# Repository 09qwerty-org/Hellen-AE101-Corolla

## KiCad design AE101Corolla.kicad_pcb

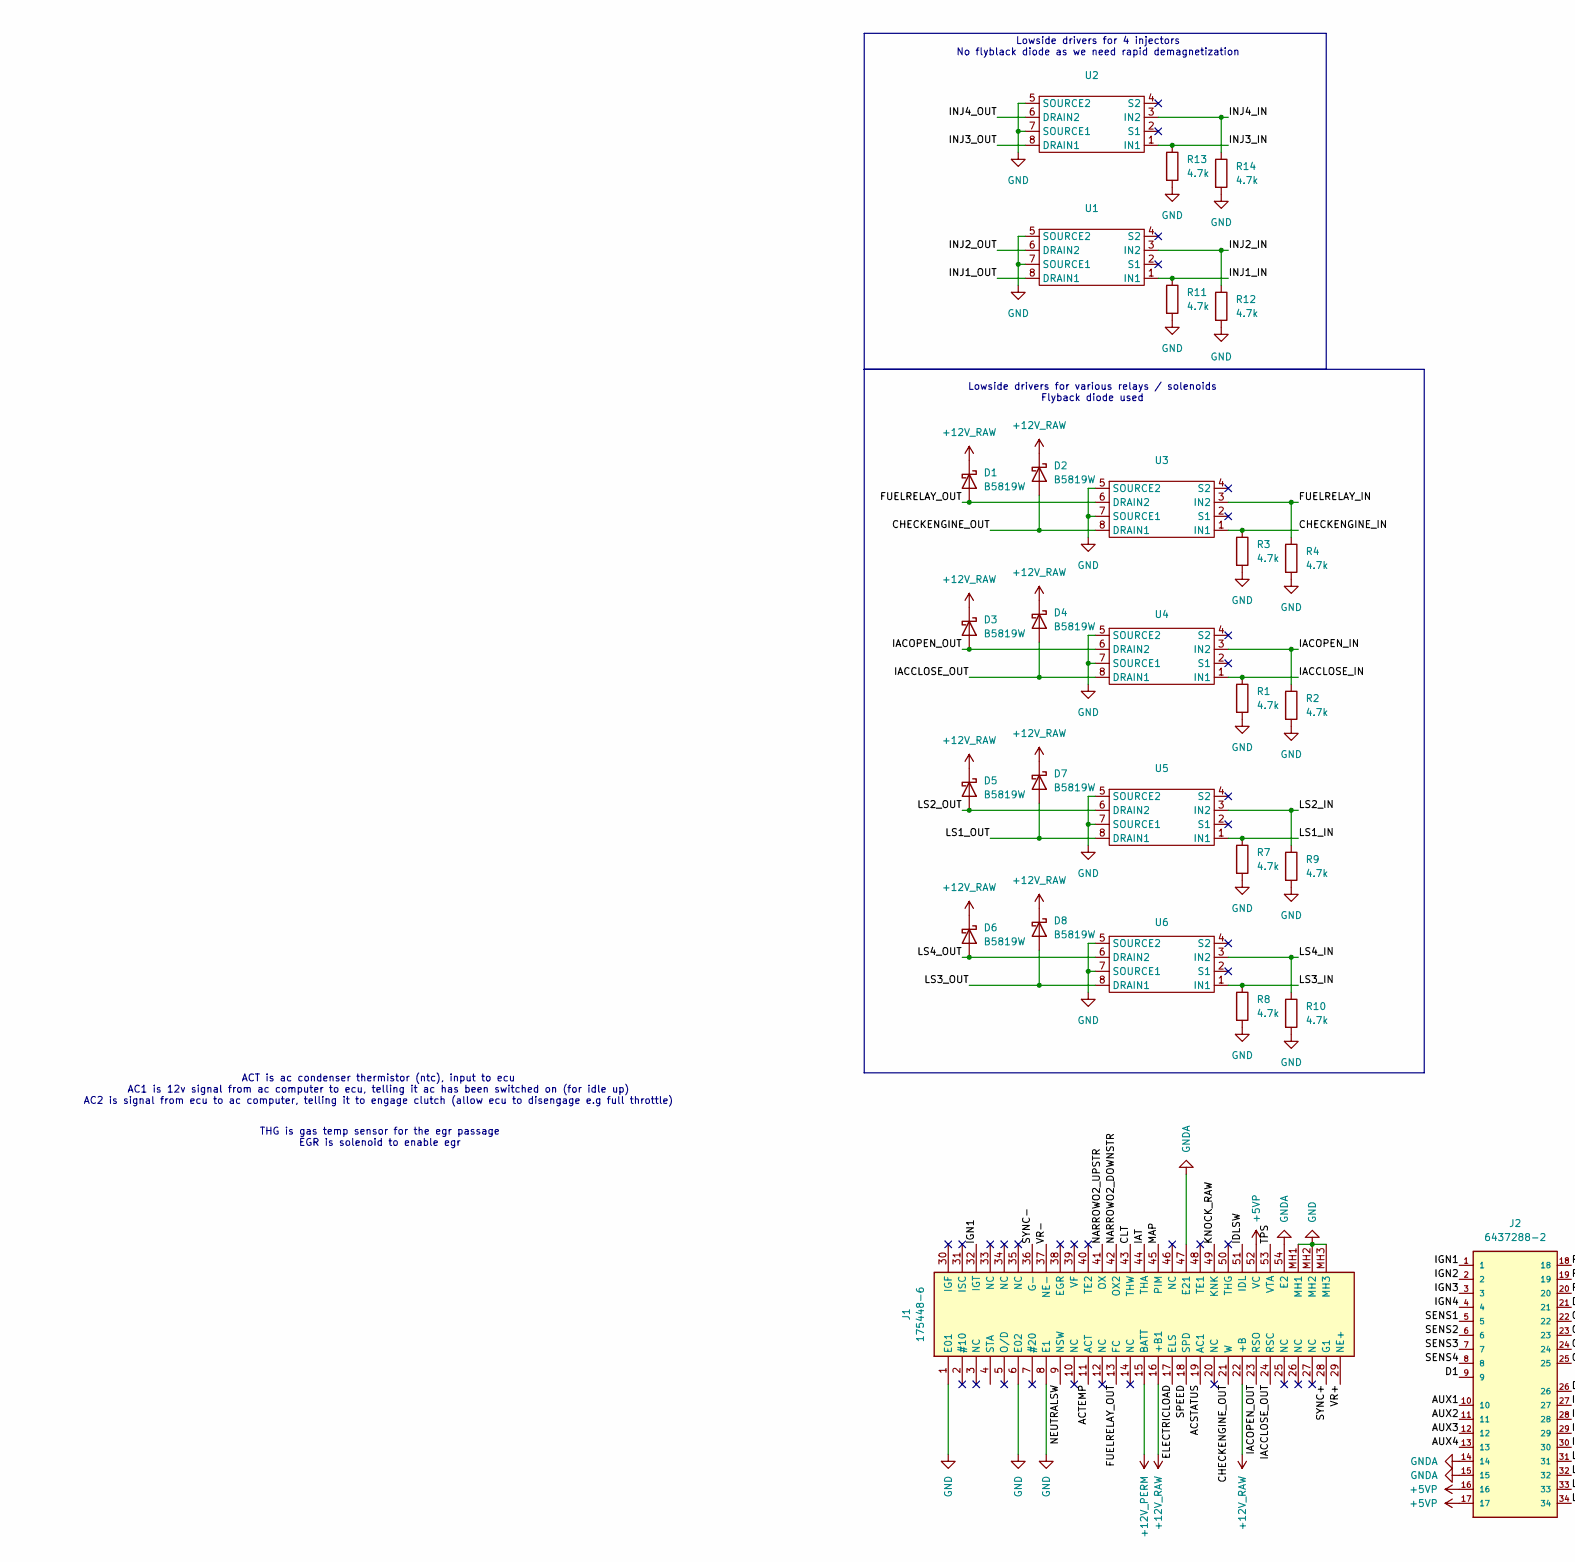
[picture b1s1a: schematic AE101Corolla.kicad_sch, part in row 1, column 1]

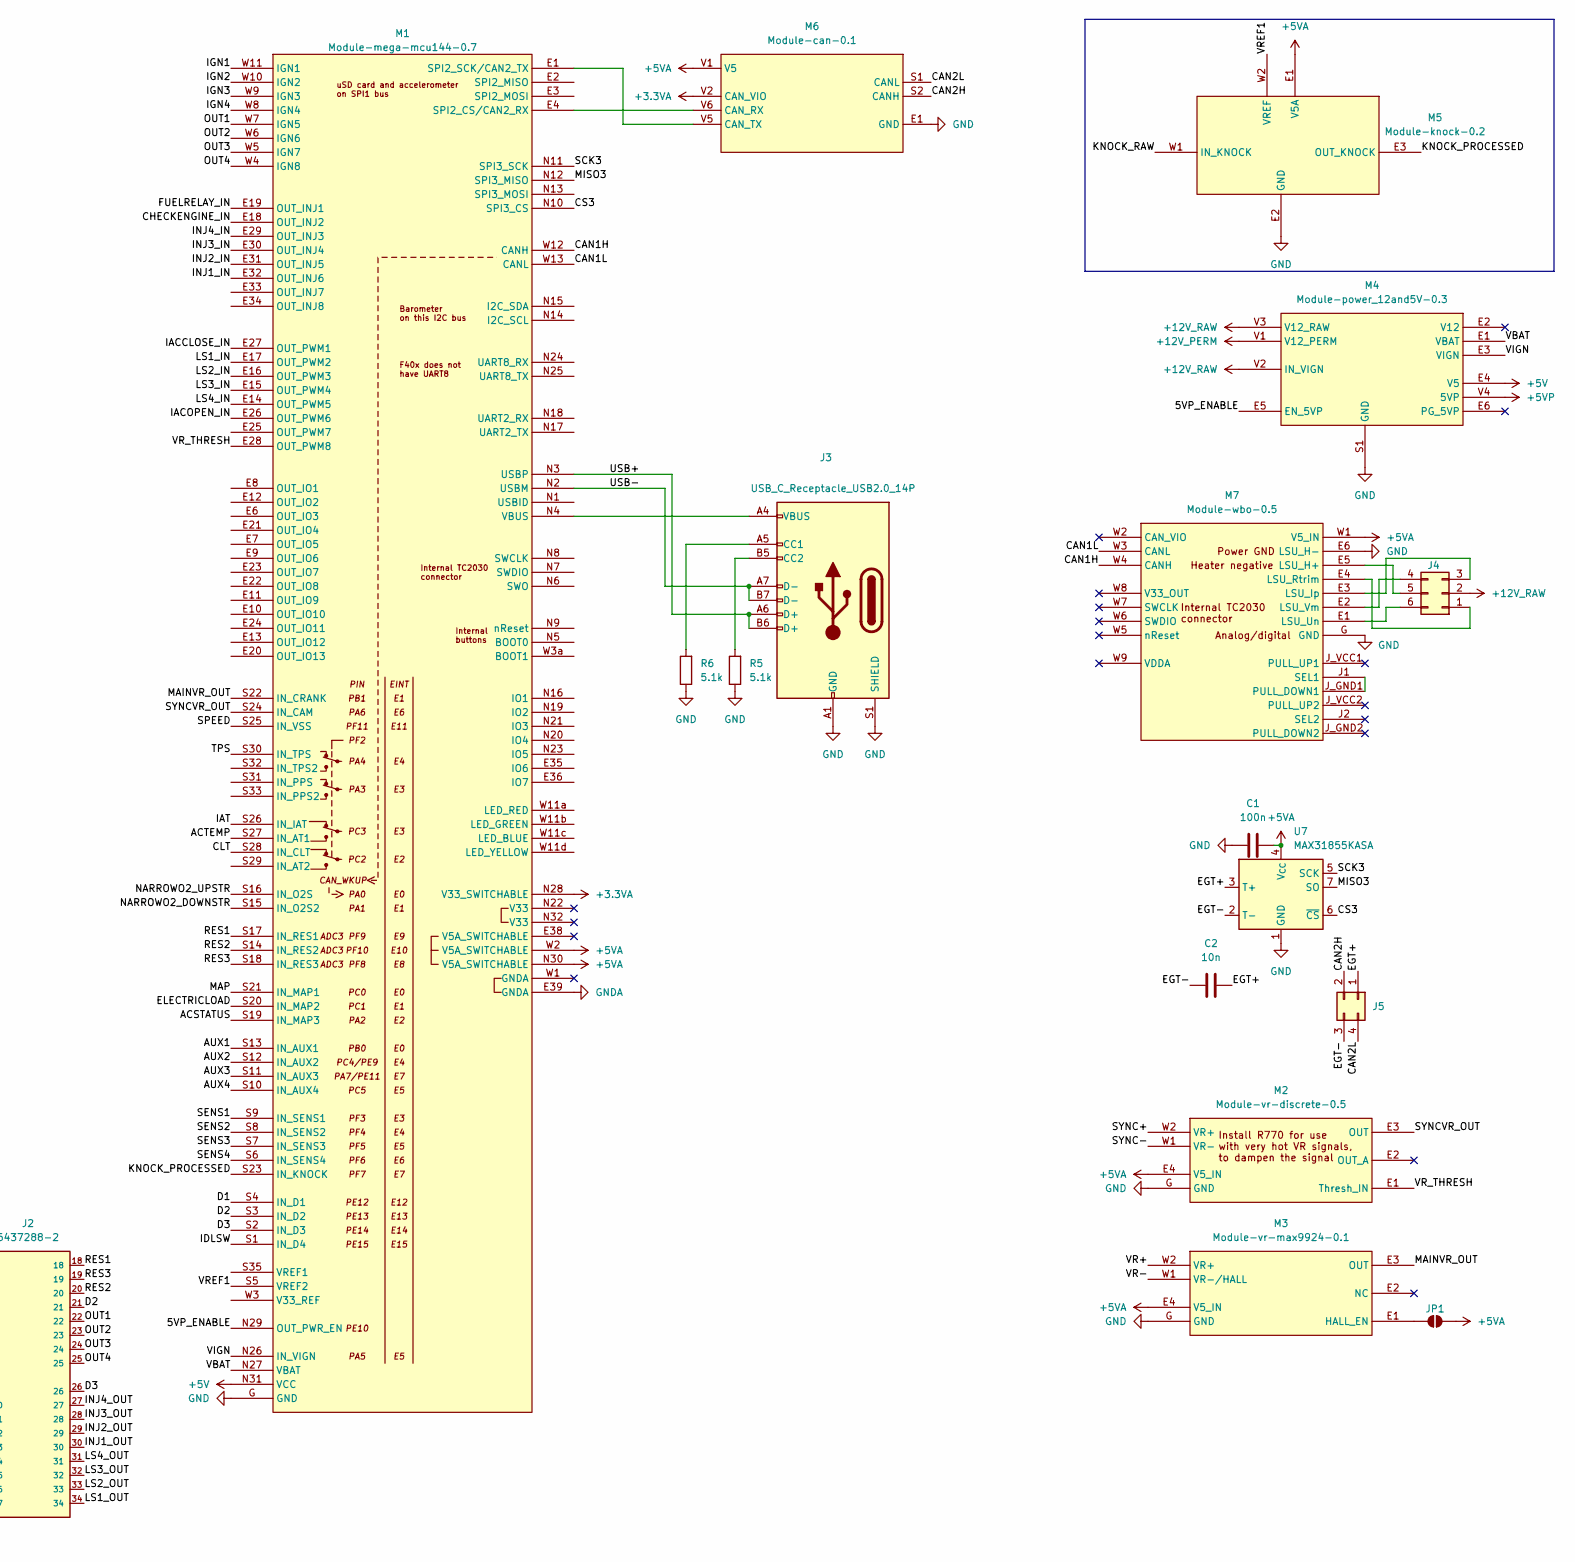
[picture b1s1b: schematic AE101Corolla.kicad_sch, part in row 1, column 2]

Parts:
C1: 100n; C_0402_1005Metric; LCSC C1525
C2: 10n; C_0402_1005Metric; LCSC C15195
D1, D2, D3, D4, D5, D6, D7, D8: B5819W; D_SOD-123; LCSC C8598
J1: 175448-6; 1754486; Mouser Part Number 571-175448-6
J2: 6437288-2; TE_6437288-2; PARTREV A1
J3: USB_C_Receptacle_USB2.0_14P; USB_C_Receptacle_GCT_USB4105-xx-A_16P_TopMnt_Horizontal
J4: Conn_02x03_Counter_Clockwise; Molex_Mini-Fit_Jr_5569-06A2_2x03_P4.20mm_Horizontal
J5: Conn_02x02_Counter_Clockwise; Molex_Mini-Fit_Jr_5569-04A2_2x02_P4.20mm_Horizontal
JP1: SolderJumper_2_Open; SolderJumper-2_P1.3mm_Open_TrianglePad1.0x1.5mm
M1: Module-mega-mcu144-0.7; mega-mcu144
M2: Module-vr-discrete-0.5; vr-discrete
M3: Module-vr-max9924-0.1; vr-max9924
M4: Module-power_12and5V-0.3; power_12and5V
M5: Module-knock-0.2; knock
M6: Module-can-0.1; can
M7: Module-wbo-0.5; wbo
R1, R2, R3, R4, R7, R8, R9, R10, R11, R12, R13, R14: 4.7k; R_0402_1005Metric; LCSC C25900
R5, R6: 5.1k; R_0402_1005Metric; LCSC C144745
U1, U2, U3, U4, U5, U6: VNLD5090-E; LCSC C222209
U7: MAX31855KASA; SOIC-8_3.9x4.9mm_P1.27mm

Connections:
+3.3VA: M1.N28 (V33_SWITCHABLE), M6.V2 (CAN_VIO)
+5V: M1.N31 (VCC), M4.E4 (V5)
+5VA: C1.1, JP1.2 (B), M1.N30 (V5A_SWITCHABLE), M1.W2 (V5A_SWITCHABLE), M2.E4 (V5_IN), M3.E4 (V5_IN), M5.E1 (V5A), M6.V1 (V5), M7.W1 (V5_IN), U7.4 (V_{CC})
+5VP: J1.52 (VC), J2.16, J2.17, M4.V4 (5VP)
+12V_PERM: J1.15 (BATT), M4.V1 (V12_PERM)
+12V_RAW: D1.1 (K), D2.1 (K), D3.1 (K), D4.1 (K), D5.1 (K), D6.1 (K), D7.1 (K), D8.1 (K), J1.16 (+B1), J1.22 (+B), J4.2, M4.V2 (IN_VIGN), M4.V3 (V12_RAW)
/5VP_ENABLE: M1.N29 (OUT_PWR_EN), M4.E5 (EN_5VP)
/ACSTATUS: J1.19 (AC1), M1.S19 (IN_MAP3)
/ACTEMP: J1.11 (ACT), M1.S27 (IN_AT1)
/AUX1: J2.10, M1.S13 (IN_AUX1)
/AUX2: J2.11, M1.S12 (IN_AUX2)
/AUX3: J2.12, M1.S11 (IN_AUX3)
/AUX4: J2.13, M1.S10 (IN_AUX4)
/CAN1H: M1.W12 (CANH), M7.W4 (CANH)
/CAN1L: M1.W13 (CANL), M7.W3 (CANL)
/CAN2H: J5.2, M6.S2 (CANH)
/CAN2L: J5.4, M6.S1 (CANL)
/CHECKENGINE_IN: M1.E18 (OUT_INJ2), R3.1, U3.1 (IN1)
/CHECKENGINE_OUT: D2.2 (A), J1.21 (W), U3.8 (DRAIN1)
/CLT: J1.43 (THW), M1.S28 (IN_CLT)
/CS3: M1.N10 (SPI3_CS), U7.6 (~CS)
/D1: J2.9, M1.S4 (IN_D1)
/D2: J2.21, M1.S3 (IN_D2)
/D3: J2.26, M1.S2 (IN_D3)
/EGT+: C2.2, J5.1, U7.3 (T+)
/EGT-: C2.1, J5.3, U7.2 (T-)
/ELECTRICLOAD: J1.17 (ELS), M1.S20 (IN_MAP2)
/FUELRELAY_IN: M1.E19 (OUT_INJ1), R4.1, U3.3 (IN2)
/FUELRELAY_OUT: D1.2 (A), J1.13 (FC), U3.6 (DRAIN2)
/IACCLOSE_IN: M1.E27 (OUT_PWM1), R1.1, U4.1 (IN1)
/IACCLOSE_OUT: D4.2 (A), J1.24 (RSC), U4.8 (DRAIN1)
/IACOPEN_IN: M1.E26 (OUT_PWM6), R2.1, U4.3 (IN2)
/IACOPEN_OUT: D3.2 (A), J1.23 (RSO), U4.6 (DRAIN2)
/IAT: J1.44 (THA), M1.S26 (IN_IAT)
/IDLSW: J1.51 (IDL), M1.S1 (IN_D4)
/IGN1: J1.32 (IGT), J2.1, M1.W11 (IGN1)
/IGN2: J2.2, M1.W10 (IGN2)
/IGN3: J2.3, M1.W9 (IGN3)
/IGN4: J2.4, M1.W8 (IGN4)
/INJ1_IN: M1.E32 (OUT_INJ6), R11.1, U1.1 (IN1)
/INJ1_OUT: J2.30, U1.8 (DRAIN1)
/INJ2_IN: M1.E31 (OUT_INJ5), R12.1, U1.3 (IN2)
/INJ2_OUT: J2.29, U1.6 (DRAIN2)
/INJ3_IN: M1.E30 (OUT_INJ4), R13.1, U2.1 (IN1)
/INJ3_OUT: J2.28, U2.8 (DRAIN1)
/INJ4_IN: M1.E29 (OUT_INJ3), R14.1, U2.3 (IN2)
/INJ4_OUT: J2.27, U2.6 (DRAIN2)
/KNOCK_PROCESSED: M1.S23 (IN_KNOCK), M5.E3 (OUT_KNOCK)
/KNOCK_RAW: J1.49 (KNK), M5.W1 (IN_KNOCK)
/LS1_IN: M1.E17 (OUT_PWM2), R7.1, U5.1 (IN1)
/LS1_OUT: D7.2 (A), J2.34, U5.8 (DRAIN1)
/LS2_IN: M1.E16 (OUT_PWM3), R9.1, U5.3 (IN2)
/LS2_OUT: D5.2 (A), J2.33, U5.6 (DRAIN2)
/LS3_IN: M1.E15 (OUT_PWM4), R8.1, U6.1 (IN1)
/LS3_OUT: D8.2 (A), J2.32, U6.8 (DRAIN1)
/LS4_IN: M1.E14 (OUT_PWM5), R10.1, U6.3 (IN2)
/LS4_OUT: D6.2 (A), J2.31, U6.6 (DRAIN2)
/MAINVR_OUT: M1.S22 (IN_CRANK), M3.E3 (OUT)
/MAP: J1.45 (PIM), M1.S21 (IN_MAP1)
/MISO3: M1.N12 (SPI3_MISO), U7.7 (SO)
/NARROWO2_DOWNSTR: J1.42 (OX2), M1.S15 (IN_O2S2)
/NARROWO2_UPSTR: J1.41 (OX), M1.S16 (IN_O2S)
/NEUTRALSW: J1.9 (NSW)
/OUT1: J2.22, M1.W7 (IGN5)
/OUT2: J2.23, M1.W6 (IGN6)
/OUT3: J2.24, M1.W5 (IGN7)
/OUT4: J2.25, M1.W4 (IGN8)
/RES1: J2.18, M1.S17 (IN_RES1)
/RES2: J2.20, M1.S14 (IN_RES2)
/RES3: J2.19, M1.S18 (IN_RES3)
/SCK3: M1.N11 (SPI3_SCK), U7.5 (SCK)
/SENS1: J2.5, M1.S9 (IN_SENS1)
/SENS2: J2.6, M1.S8 (IN_SENS2)
/SENS3: J2.7, M1.S7 (IN_SENS3)
/SENS4: J2.8, M1.S6 (IN_SENS4)
/SPEED: J1.18 (SPD), M1.S25 (IN_VSS)
/SYNC+: J1.28 (G1), M2.W2 (VR+)
/SYNC-: J1.36 (G-), M2.W1 (VR-)
/SYNCVR_OUT: M1.S24 (IN_CAM), M2.E3 (OUT)
/TPS: J1.53 (VTA), M1.S30 (IN_TPS)
/USB+: J3.A6 (D+), J3.B6 (D+), M1.N3 (USBP)
/USB-: J3.A7 (D-), J3.B7 (D-), M1.N2 (USBM)
/VBAT: M1.N27 (VBAT), M4.E1 (VBAT)
/VIGN: M1.N26 (IN_VIGN), M4.E3 (VIGN)
/VR+: J1.29 (NE+), M3.W2 (VR+)
/VR-: J1.37 (NE-), M3.W1 (VR-/HALL)
/VREF1: M1.S5 (VREF2), M5.W2 (VREF)
/VR_THRESH: M1.E28 (OUT_PWM8), M2.E1 (Thresh_IN)
GND: C1.2, J1.1 (E01), J1.6 (E02), J1.8 (E1), J1.MH1, J1.MH2, J1.MH3, J3.A1 (GND), J3.A12 (GND), J3.B1 (GND), J3.B12 (GND), J3.S1 (SHIELD), M1.G (GND), M2.G (GND), M3.G (GND), M4.S1 (GND), M5.E2 (GND), M6.E1 (GND), M7.E6 (LSU_H-), M7.G (GND), R1.2, R2.2, R3.2, R4.2, R5.1, R6.1, R7.2, R8.2, R9.2, R10.2, R11.2, R12.2, R13.2, R14.2, U1.5 (SOURCE2), U1.7 (SOURCE1), U2.5 (SOURCE2), U2.7 (SOURCE1), U3.5 (SOURCE2), U3.7 (SOURCE1), U4.5 (SOURCE2), U4.7 (SOURCE1), U5.5 (SOURCE2), U5.7 (SOURCE1), U6.5 (SOURCE2), U6.7 (SOURCE1), U7.1 (GND)
GNDA: J1.47 (E21), J1.54 (E2), J2.14, J2.15, M1.E39 (GNDA)
unnamed: J3.A5 (CC1), R6.2
unnamed: J3.B5 (CC2), R5.2
unnamed: J4.1, M7.E4 (LSU_Rtrim)
unnamed: J4.3, M7.E3 (LSU_Ip)
unnamed: J4.4, M7.E2 (LSU_Vm)
unnamed: J4.5, M7.E5 (LSU_H+)
unnamed: J4.6, M7.E1 (LSU_Un)
unnamed: JP1.1 (A), M3.E1 (HALL_EN)
unnamed: M1.E4 (SPI2_CS/CAN2_RX), M6.V6 (CAN_RX)
unnamed: M1.E1 (SPI2_SCK/CAN2_TX), M6.V5 (CAN_TX)
unnamed: J3.A4 (VBUS), J3.A9 (VBUS), J3.B4 (VBUS), J3.B9 (VBUS), M1.N4 (VBUS)
unnamed: M7.J1 (SEL1), M7.J_GND1 (PULL_DOWN1)

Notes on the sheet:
ACT is ac condenser thermistor (ntc), input to ecu AC1 is 12v signal from ac computer to ecu, telling it ac has been switched on (for idle up) AC2 is signal from ecu to ac computer, telling it to engage clutch (allow ecu to disengage e.g full throttle)
Lowside drivers for various relays / solenoids Flyback diode used
Lowside drivers for 4 injectors No flyblack diode as we need rapid demagnetization
THG is gas temp sensor for the egr passage EGR is solenoid to enable egr

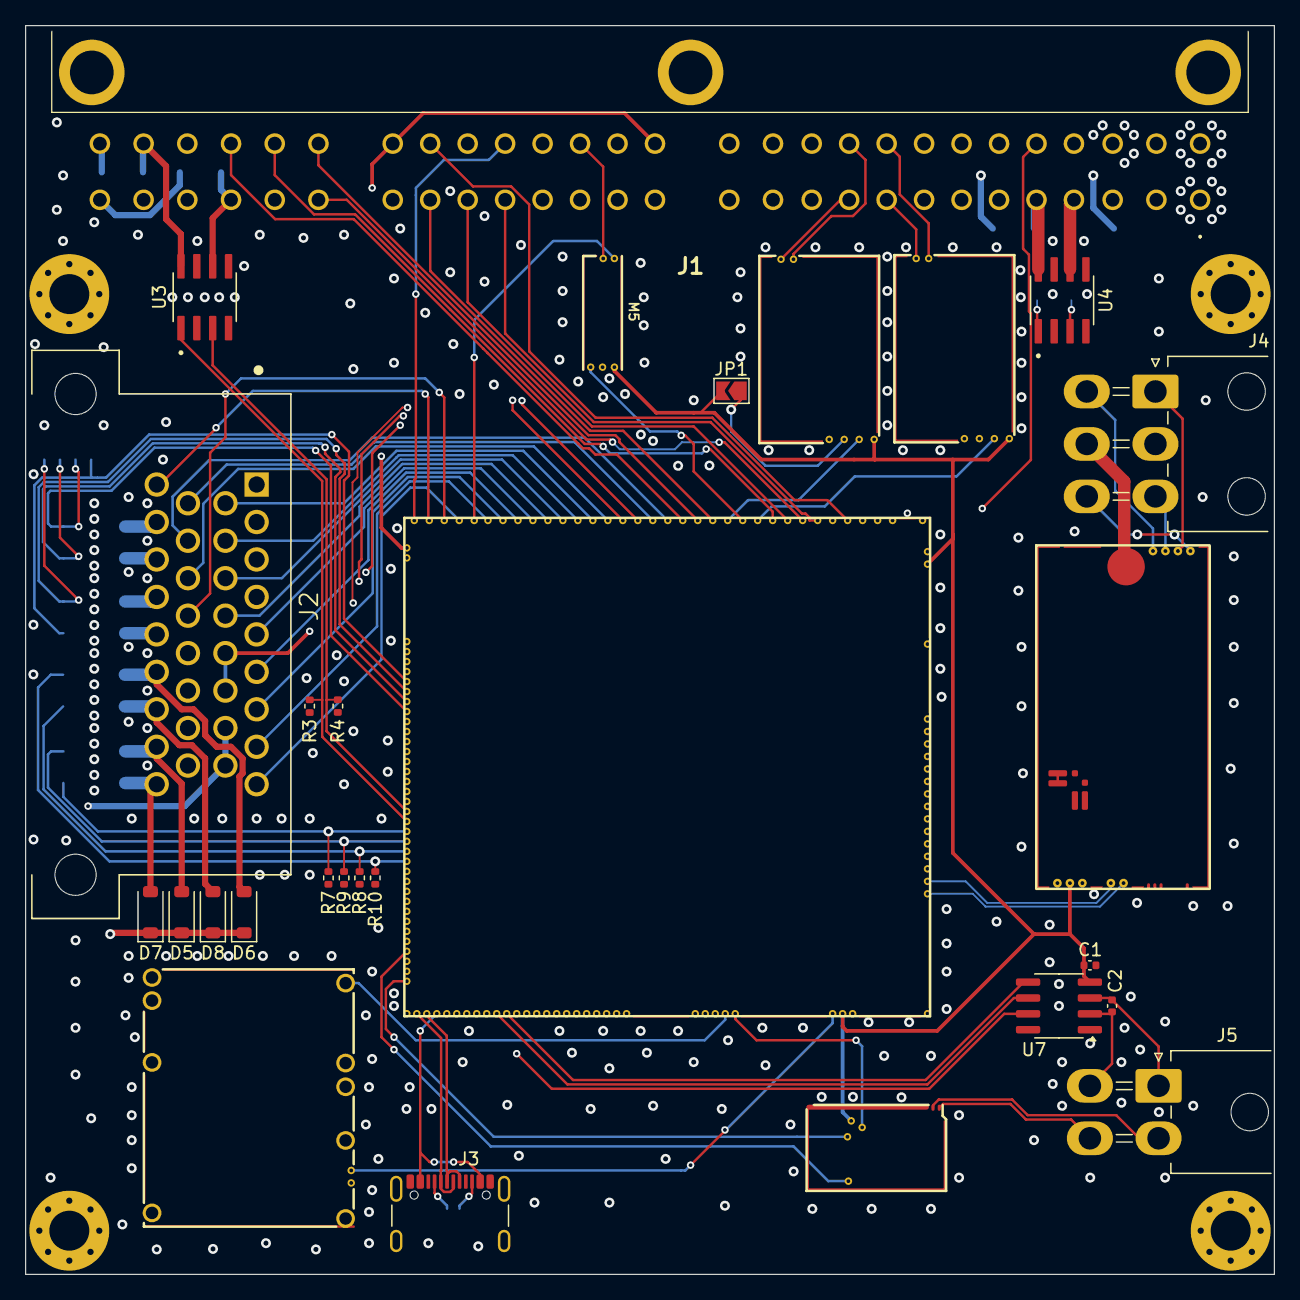
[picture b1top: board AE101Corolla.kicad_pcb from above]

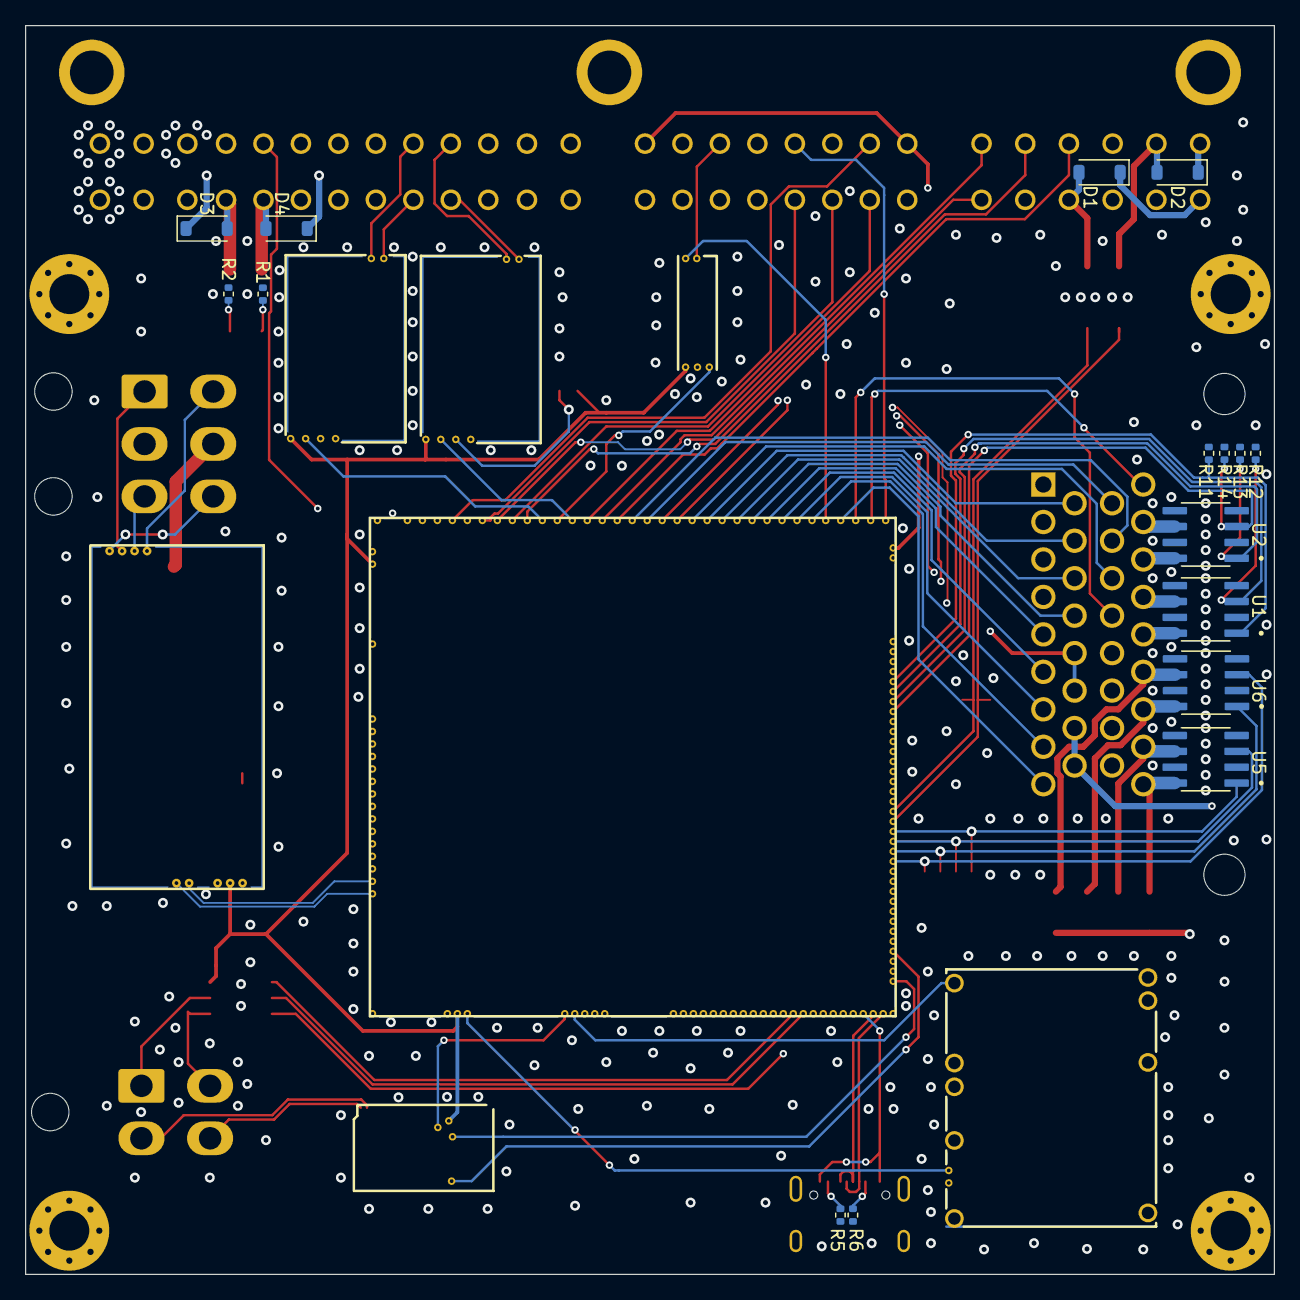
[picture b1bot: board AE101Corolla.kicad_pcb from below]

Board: 4 copper layers, 100.0 x 100.0 mm, 44 parts (16 on the bottom side), 101 nets.

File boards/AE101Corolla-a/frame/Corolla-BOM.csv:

Comment,Designator,Footprint,LCSC Part #
"100n","C1","C0402","C1525"
"10n","C2","C0402","C15195"
"B5819W","D1","D_SOD-123","C8598"
"B5819W","D2","D_SOD-123","C8598"
"B5819W","D3","D_SOD-123","C8598"
"B5819W","D4","D_SOD-123","C8598"
"B5819W","D5","D_SOD-123","C8598"
"B5819W","D6","D_SOD-123","C8598"
"B5819W","D7","D_SOD-123","C8598"
"B5819W","D8","D_SOD-123","C8598"
"175448-6","J1","1754486",""
"6437288-2","J2","TE_6437288-2",""
"USB_C_Receptacle_USB2.0_14P","J3","USB_C_Receptacle_GCT_USB4105-xx-A_16P_TopMnt_Horizontal",""
"Conn_02x03_Counter_Clockwise","J4","Molex_Mini-Fit_Jr_5569-06A2_2x03_P4.20mm_Horizontal",""
"Conn_02x02_Counter_Clockwise","J5","Molex_Mini-Fit_Jr_5569-04A2_2x02_P4.20mm_Horizontal",""
"Module:mega-mcu144/0.7","M1","mega-mcu144",""
"Module:vr-discrete/0.5","M2","vr-discrete",""
"Module:vr-max9924/0.1","M3","vr-max9924",""
"Module:power_12and5V/0.3","M4","power_12and5V",""
"Module:knock/0.2","M5","knock",""
"Module:can/0.1","M6","can",""
"Module:wbo/0.5","M7","wbo",""
"4.7k","R1","R0402","C25900"
"4.7k","R2","R0402","C25900"
"4.7k","R3","R0402","C25900"
"4.7k","R4","R0402","C25900"
"5.1k","R5","R0402","C144745"
"5.1k","R6","R0402","C144745"
"4.7k","R7","R0402","C25900"
"4.7k","R8","R0402","C25900"
"4.7k","R9","R0402","C25900"
"4.7k","R10","R0402","C25900"
"~","U1","VNLD5090-E","C222209"
"~","U2","VNLD5090-E","C222209"
"~","U3","VNLD5090-E","C222209"
"~","U4","VNLD5090-E","C222209"
"~","U5","VNLD5090-E","C222209"
"~","U6","VNLD5090-E","C222209"
"MAX31855KASA","U7","SO8",""

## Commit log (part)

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2026-01-30 GHA says update kicad6-libraries
2026-02-08 GHA says update hellen-one
2026-02-10 sync
2026-02-13 [skip actions] Auto-generated board v2.1
2026-02-13 add shoddy script for lcsc component quantity
